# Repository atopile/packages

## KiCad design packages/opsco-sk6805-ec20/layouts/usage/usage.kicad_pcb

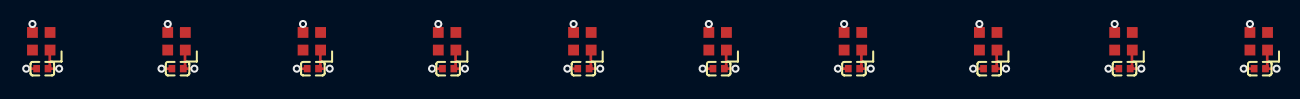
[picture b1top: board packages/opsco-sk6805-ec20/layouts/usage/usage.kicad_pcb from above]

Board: 2 copper layers, 20 parts (0 on the bottom side), 11 nets.

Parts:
C1, C2, C3, C4, C5, C6, C7, C8, C9, C10: 100nF ±10%; C0402
LED1, LED2, LED3, LED4, LED5, LED6, LED7, LED8, LED9, LED10: LED-SMD_4P-L2.0-W2.0-BR

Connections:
hv: C1.1, C2.1, C3.1, C4.1, C5.1, C6.1, C7.1, C8.1, C9.1, C10.1, LED1.1, LED2.1, LED3.1, LED4.1, LED5.1, LED6.1, LED7.1, LED8.1, LED9.1, LED10.1
leds[1]-data_in-DIN: LED1.2, LED2.4
leds[2]-data_in-DIN: LED2.2, LED3.4
leds[3]-data_in-DIN: LED3.2, LED4.4
leds[4]-data_in-DIN: LED4.2, LED5.4
leds[5]-data_in-DIN: LED5.2, LED6.4
leds[6]-data_in-DIN: LED6.2, LED7.4
leds[7]-data_in-DIN: LED7.2, LED8.4
leds[8]-data_in-DIN: LED8.2, LED9.4
leds[9]-data_in-DIN: LED9.2, LED10.4
lv: C1.2, C2.2, C3.2, C4.2, C5.2, C6.2, C7.2, C8.2, C9.2, C10.2, LED1.3, LED2.3, LED3.3, LED4.3, LED5.3, LED6.3, LED7.3, LED8.3, LED9.3, LED10.3

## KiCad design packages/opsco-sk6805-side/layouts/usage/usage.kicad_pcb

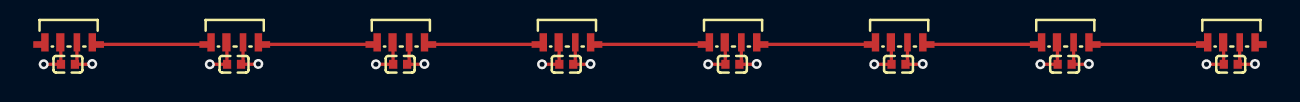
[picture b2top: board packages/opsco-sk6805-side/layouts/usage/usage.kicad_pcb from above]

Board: 2 copper layers, 16 parts (0 on the bottom side), 9 nets.

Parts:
C1, C2, C3, C4, C5, C6, C7, C8: 100nF ±10%; C0402
U1, U2, U3, U4, U5, U6, U7, U8: LED-SMD_4P-L3.5-W1.6_SK6805SIDE-G-001

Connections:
edge_leds[1]-data_in-DIN: U1.1, U2.4
edge_leds[2]-data_in-DIN: U2.1, U3.4
edge_leds[3]-data_in-DIN: U3.1, U4.4
edge_leds[4]-data_in-DIN: U4.1, U5.4
edge_leds[5]-data_in-DIN: U5.1, U6.4
edge_leds[6]-data_in-DIN: U6.1, U7.4
edge_leds[7]-data_in-DIN: U7.1, U8.4
hv: C1.1, C2.1, C3.1, C4.1, C5.1, C6.1, C7.1, C8.1, U1.3, U2.3, U3.3, U4.3, U5.3, U6.3, U7.3, U8.3
lv: C1.2, C2.2, C3.2, C4.2, C5.2, C6.2, C7.2, C8.2, U1.2, U2.2, U3.2, U4.2, U5.2, U6.2, U7.2, U8.2

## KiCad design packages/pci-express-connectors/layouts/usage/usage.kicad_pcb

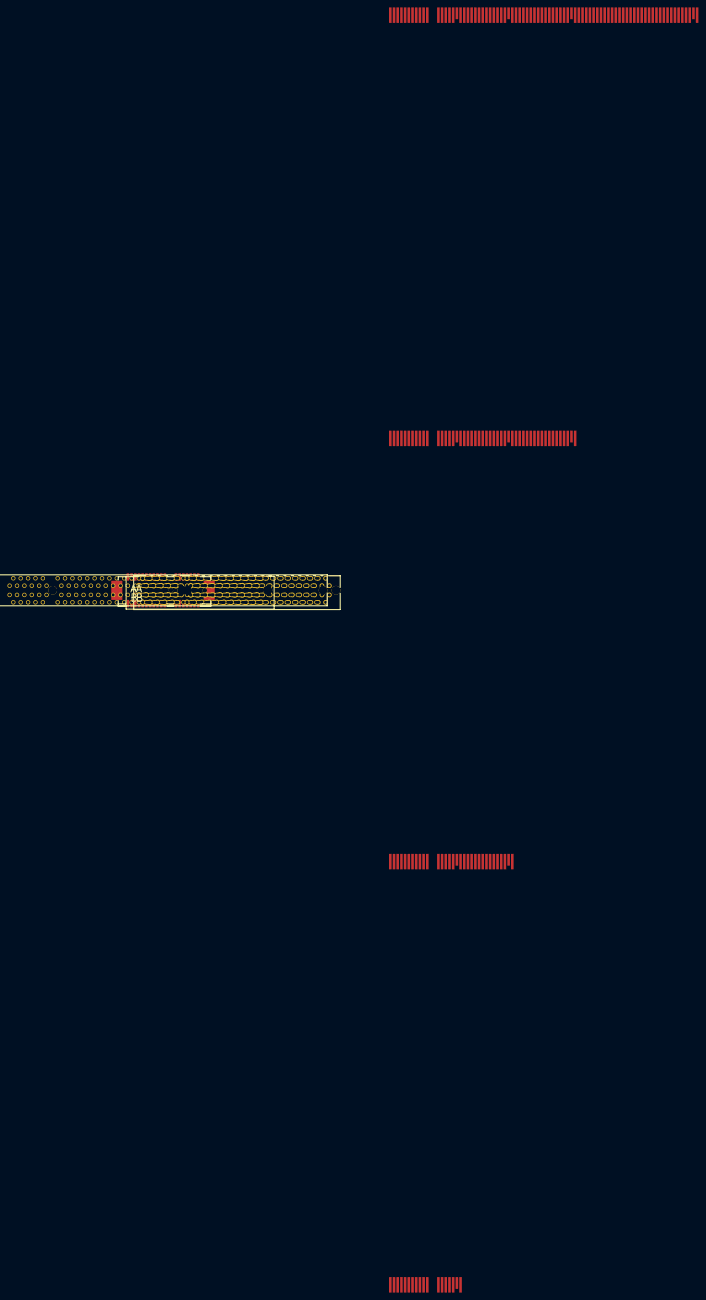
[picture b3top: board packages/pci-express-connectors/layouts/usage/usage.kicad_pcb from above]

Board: 2 copper layers, 8 parts (0 on the bottom side), 7 nets, no tracks yet.

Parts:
CN1: CONN-TH_64P-P1.00-V_3183-XXXXXPXT
CN2: CONN-TH_98P-P1.00-V_3183-XXXXXPXT
CN3: CONN-TH_2EG08217-D2D-DF
J1: PCIexpress_x1
J2: PCIexpress_x4
J3: PCIexpress_x8
J4: PCIexpress_x16
U1: CONN-SMD_X3113WVS-36-9TV01

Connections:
GND: CN3.4, CN3.12, CN3.15, CN3.18, J1.A4, J1.A12, J1.A15, J1.A18, J1.B4, J1.B7, J1.B13, J1.B16, J1.B18, J2.A4, J2.A12, J2.A15, J2.A18, J2.A20, J2.A23, J2.A24, J2.A27, J2.A28, J2.A31, J2.B4, J2.B7, J2.B13, J2.B16, J2.B18, J2.B21, J2.B22, J2.B25, J2.B26, J2.B29, J2.B32, J3.A4, J3.A12, J3.A15, J3.A18, J3.A20, J3.A23, J3.A24, J3.A27, J3.A28, J3.A31, J3.A34, J3.A37, J3.A38, J3.A41, J3.A42, J3.A45, J3.A46, J3.A49, J3.B4, J3.B7, J3.B13, J3.B16, J3.B18, J3.B21, J3.B22, J3.B25, J3.B26, J3.B29, J3.B32, J3.B35, J3.B36, J3.B39, J3.B40, J3.B43, J3.B44, J3.B47, J3.B49, J4.A4, J4.A12, J4.A15, J4.A18, J4.A20, J4.A23, J4.A24, J4.A27, J4.A28, J4.A31, J4.A34, J4.A37, J4.A38, J4.A41, J4.A42, J4.A45, J4.A46, J4.A49, J4.A51, J4.A54, J4.A55, J4.A58, J4.A59, J4.A62, J4.A63, J4.A66, J4.A67, J4.A70, J4.A71, J4.A74, J4.A75, J4.A78, J4.A79, J4.A82, J4.B4, J4.B7, J4.B13, J4.B16, J4.B18, J4.B21, J4.B22, J4.B25, J4.B26, J4.B29, J4.B32, J4.B35, J4.B36, J4.B39, J4.B40, J4.B43, J4.B44, J4.B47, J4.B49, J4.B52, J4.B53, J4.B56, J4.B57, J4.B60, J4.B61, J4.B64, J4.B65, J4.B68, J4.B69, J4.B72, J4.B73, J4.B76, J4.B77, J4.B80, J4.B82, U1.4, U1.12, U1.15, U1.18, U1.22, U1.25, U1.31, U1.34, U1.36
main_3v3-VCC: CN3.9, CN3.10, J1.A9, J1.A10, J1.B8, J2.A9, J2.A10, J2.B8, J3.A9, J3.A10, J3.B8, J4.A9, J4.A10, J4.B8, U1.9, U1.10, U1.26
main_3v3_aux-VCC: J1.B10, J2.B10, J3.B10, J4.B10, U1.28
main_12v-VCC: CN3.2, CN3.3, J1.A2, J1.A3, J1.B1, J1.B2, J1.B3, J2.A2, J2.A3, J2.B1, J2.B2, J2.B3, J3.A2, J3.A3, J3.B1, J3.B2, J3.B3, J4.A2, J4.A3, J4.B1, J4.B2, J4.B3, U1.2, U1.3, U1.19, U1.20, U1.21
pcie_x4_card-signals-B17: J2.B17, J2.B31
pcie_x8_card-signals-B17: J3.B17, J3.B31, J3.B48
pcie_x16_card-signals-B17: J4.B17, J4.B31, J4.B48, J4.B81
